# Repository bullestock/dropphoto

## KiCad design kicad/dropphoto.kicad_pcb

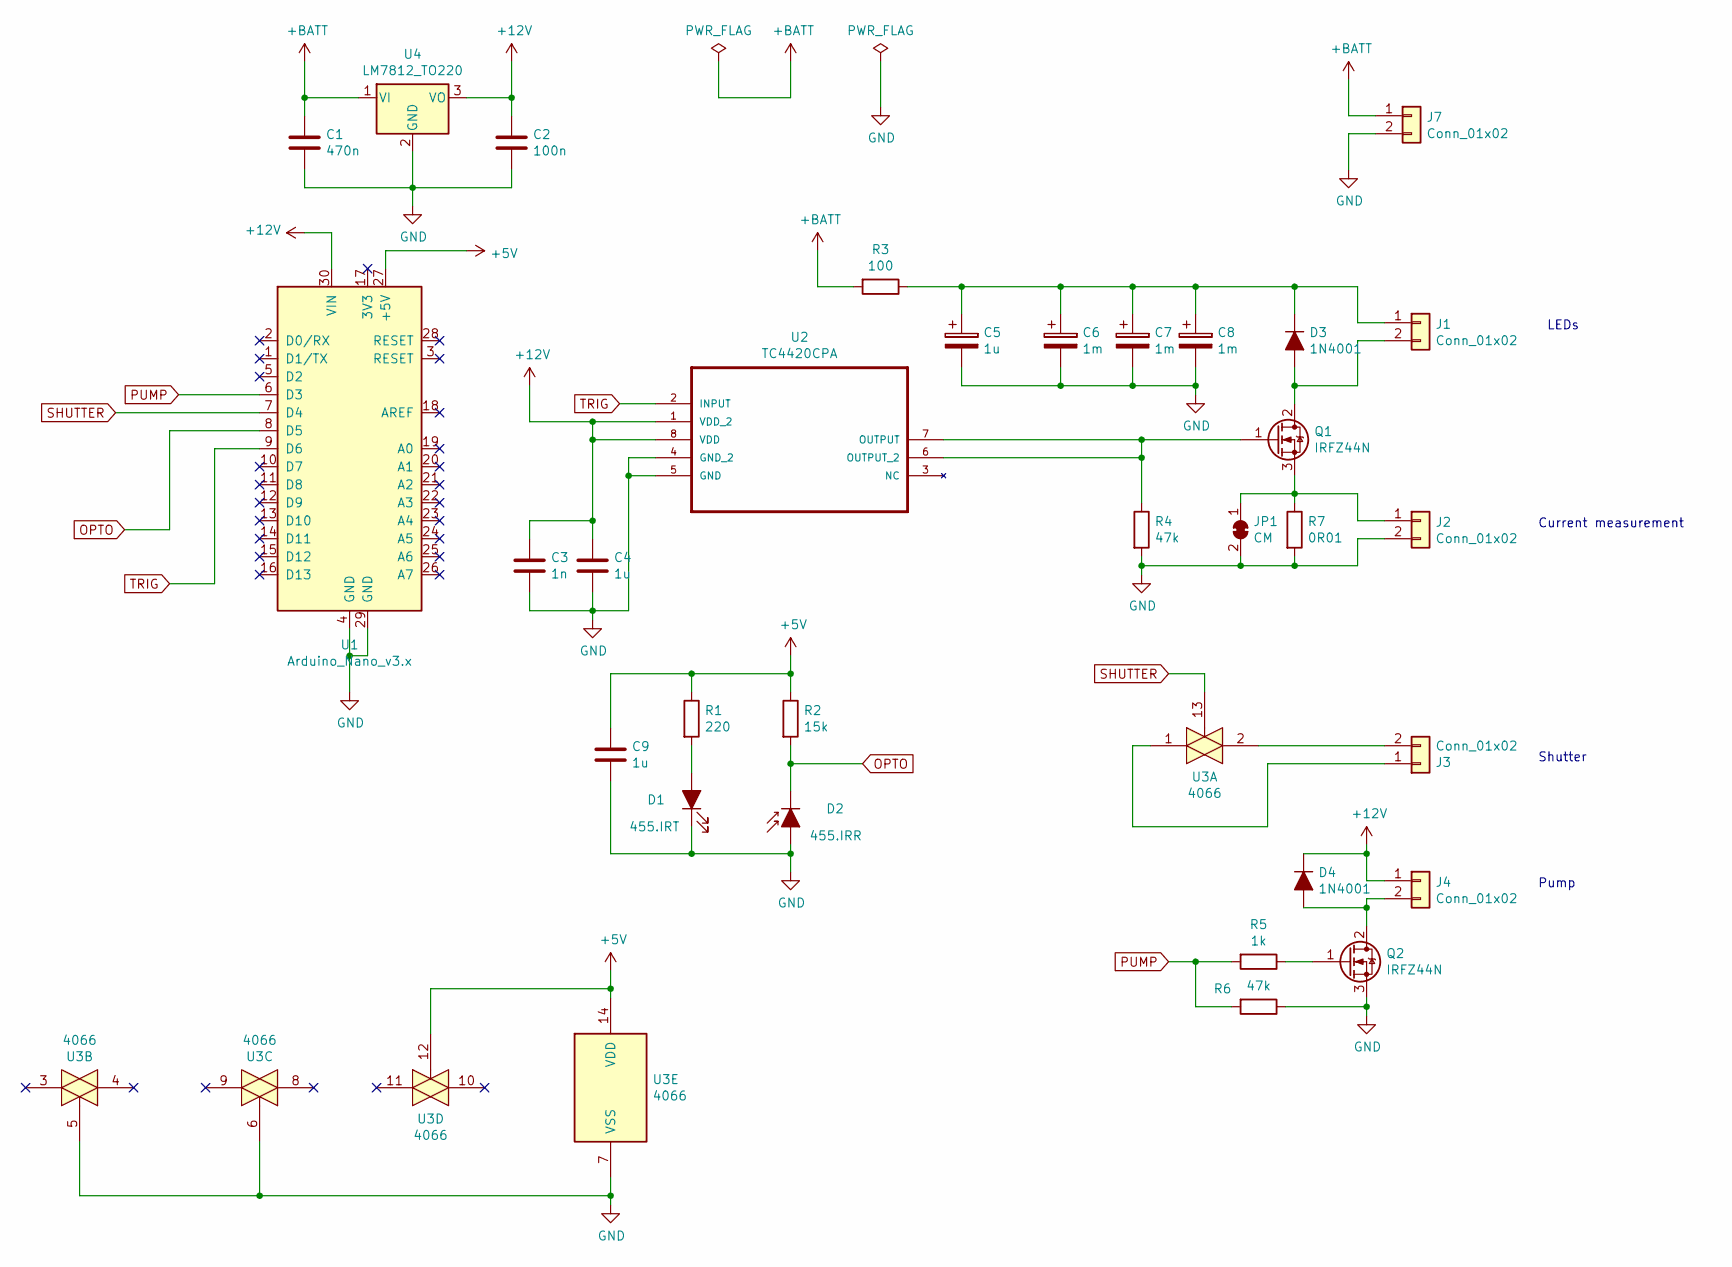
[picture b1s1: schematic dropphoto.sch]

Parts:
C1: 470n; C_Rect_L7.2mm_W5.5mm_P5.00mm_FKS2_FKP2_MKS2_MKP2
C2: 100n; C_Rect_L7.2mm_W5.5mm_P5.00mm_FKS2_FKP2_MKS2_MKP2
C3: 1n; C_Rect_L7.0mm_W2.0mm_P5.00mm
C4, C5, C9: 1u; C_Rect_L7.2mm_W5.5mm_P5.00mm_FKS2_FKP2_MKS2_MKP2
C6, C7, C8: 1m; C_Radial_D12.5mm_H25.0mm_P5.00mm
D1: 455.IRT; LED_D5.0mm_Horizontal_O1.27mm_Z3.0mm_IRBlack
D2: 455.IRR; LED_D5.0mm_Horizontal_O1.27mm_Z3.0mm_IRBlack
D3, D4: 1N4001; D_A-405_P12.70mm_Horizontal
J1, J2, J3, J4, J7: Conn_01x02; JST_XH_B02B-XH-A_1x02_P2.50mm_Vertical
JP1: CM; SolderJumper-2_P1.3mm_Bridged_RoundedPad1.0x1.5mm
Q1, Q2: IRFZ44N; TO-220-3_Vertical
R1: 220; R_Axial_DIN0414_L11.9mm_D4.5mm_P15.24mm_Horizontal
R2: 15k; R_Axial_DIN0414_L11.9mm_D4.5mm_P15.24mm_Horizontal
R3: 100; R_Axial_DIN0414_L11.9mm_D4.5mm_P15.24mm_Horizontal
R4, R6: 47k; R_Axial_DIN0414_L11.9mm_D4.5mm_P15.24mm_Horizontal
R5: 1k; R_Axial_DIN0414_L11.9mm_D4.5mm_P15.24mm_Horizontal
R7: 0R01; R_2512_6332Metric
U1: Arduino_Nano_v3.x; Arduino_Nano
U2: TC4420CPA; DIP-8_W7.62mm_LongPads
U3: 4066; DIP-14_W7.62mm_LongPads
U4: LM7812_TO220; TO-220-3_Vertical

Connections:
+5V: C9.1, R1.1, R2.1, U1.27 (+5V), U3.12, U3.14 (VDD)
+12V: C2.1, C3.1, C4.1, D4.1 (K), J4.1, U1.30 (VIN), U2.1 (VDD_2), U2.8 (VDD), U4.3 (VO)
+BATT: C1.1, J7.1, R3.2, U4.1 (VI)
GND: C1.2, C2.2, C3.2, C4.2, C5.2, C6.2, C7.2, C8.2, C9.2, D1.1 (K), D2.2 (A), J2.2, J7.2, JP1.2 (B), Q2.3 (S), R4.2, R6.1, R7.2, U1.4 (GND), U1.29 (GND), U2.4 (GND_2), U2.5 (GND), U3.5, U3.6, U3.7 (VSS), U4.2 (GND)
unnamed: C5.1, C6.1, C7.1, C8.1, D3.1 (K), J1.1, R3.1
unnamed: D1.2 (A), R1.2
unnamed: D3.2 (A), J1.2, Q1.2 (D)
unnamed: D4.2 (A), J4.2, Q2.2 (D)
unnamed: J2.1, JP1.1 (A), Q1.3 (S), R7.1
unnamed: J3.1, U3.1
unnamed: J3.2, U3.2
unnamed: Q1.1 (G), R4.1, U2.6 (OUTPUT_2), U2.7 (OUTPUT)
unnamed: Q2.1 (G), R5.1
OPTO: D2.1 (K), R2.2, U1.8 (D5)
PUMP: R5.2, R6.2, U1.6 (D3)
SHUTTER: U1.7 (D4), U3.13
TRIG: U1.9 (D6), U2.2 (INPUT)

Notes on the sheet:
LEDs
Current measurement
Shutter
Pump

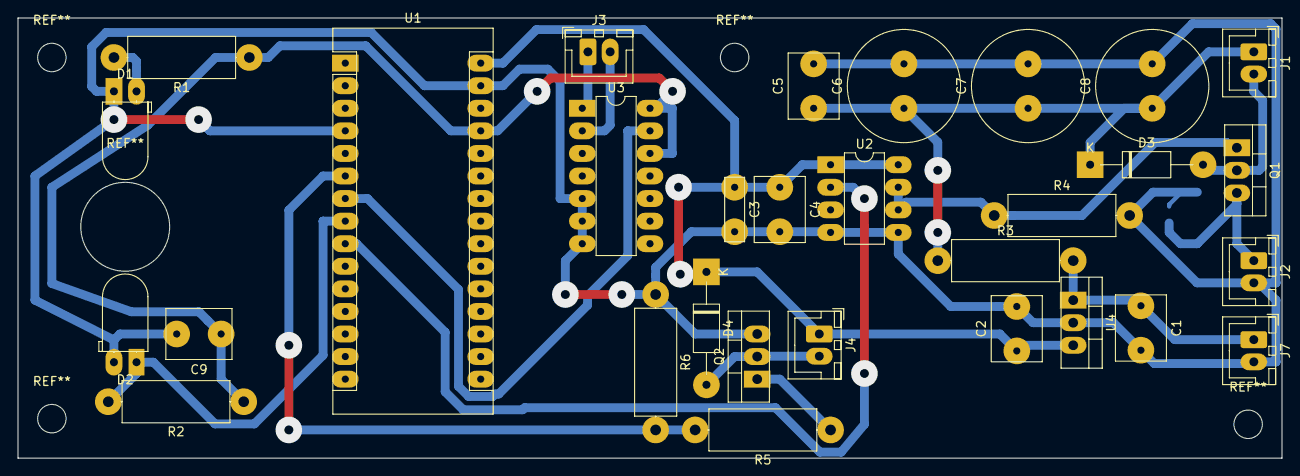
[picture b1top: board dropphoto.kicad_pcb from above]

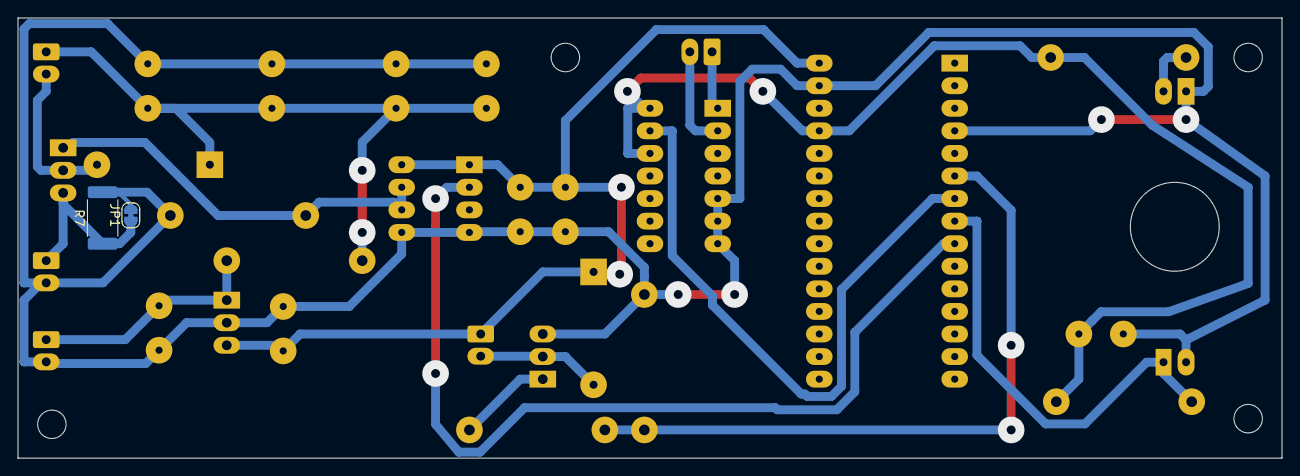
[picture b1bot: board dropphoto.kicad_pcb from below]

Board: 2 copper layers, 142.2 x 49.5 mm, 32 parts (2 on the bottom side), 17 nets.

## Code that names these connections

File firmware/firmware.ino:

#include <Arduino.h> 

constexpr int pin_pump = 3;
constexpr int pin_shutter = 4;
constexpr int pin_opto = 5;
constexpr int pin_trig = 6;

void setup()
{
    pinMode(pin_pump, OUTPUT);
    pinMode(pin_shutter, OUTPUT);
    pinMode(pin_opto, INPUT);
    pinMode(pin_trig, OUTPUT);

    Serial.begin(115200);
    Serial.println("dropphoto controller");
}

void loop()
{
    Serial.println("pump");
    for (int i = 0; i < 10; ++i)
    {
        digitalWrite(pin_pump, 0);
        delay(500);
        digitalWrite(pin_pump, 1);
        delay(500);
    }
    digitalWrite(pin_pump, 0);
    Serial.println("shutter");
    for (int i = 0; i < 10; ++i)
    {
        digitalWrite(pin_shutter, 0);
        delay(500);
        digitalWrite(pin_shutter, 1);
        delay(500);
    }
    digitalWrite(pin_shutter, 0);
    Serial.println("trig");
    for (int i = 0; i < 10; ++i)
    {
        digitalWrite(pin_trig, 0);
        delay(500);
        digitalWrite(pin_trig, 1);
        delay(500);
    }
    digitalWrite(pin_trig, 0);
    Serial.println("opto");
    for (int i = 0; i < 100; ++i)
    {
        Serial.println(digitalRead(pin_opto));
        delay(100);
    }
}

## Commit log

2019-06-08 Add KiCAD.
2019-06-09 Complete diagram.
2019-06-15 Fix errors.
2019-06-15 Start defining footprints.
2019-06-16 Finish footprints.
2019-06-22 Enlarge footprints.
2019-06-22 Finish routing.
2020-04-18 Add test firmware.
